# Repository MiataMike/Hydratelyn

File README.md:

# Hydratelyn
This project is a soil moisture sensor that can be interfaced to a MyDAQ, or just about any DAQ with a voltage input

## Probe selection
Most soil probes are made from PCB material, with ENIG plating (at best), which corrodes over time due to electrolysis
Hydratelyn uses 2mm pencil leads as the probes, which won't rust. The resistance of the probes was measured around 15 Ohms
from end to end, which is insignificant relative to the resistance of the soil

## Soil resistance
To figure out what resistance range we're trying to measure, I placed 2 leads in my plants' soil while it was dry and checked with a multimeter. It read 30M, which is very high. After watering it dropped to 7k.

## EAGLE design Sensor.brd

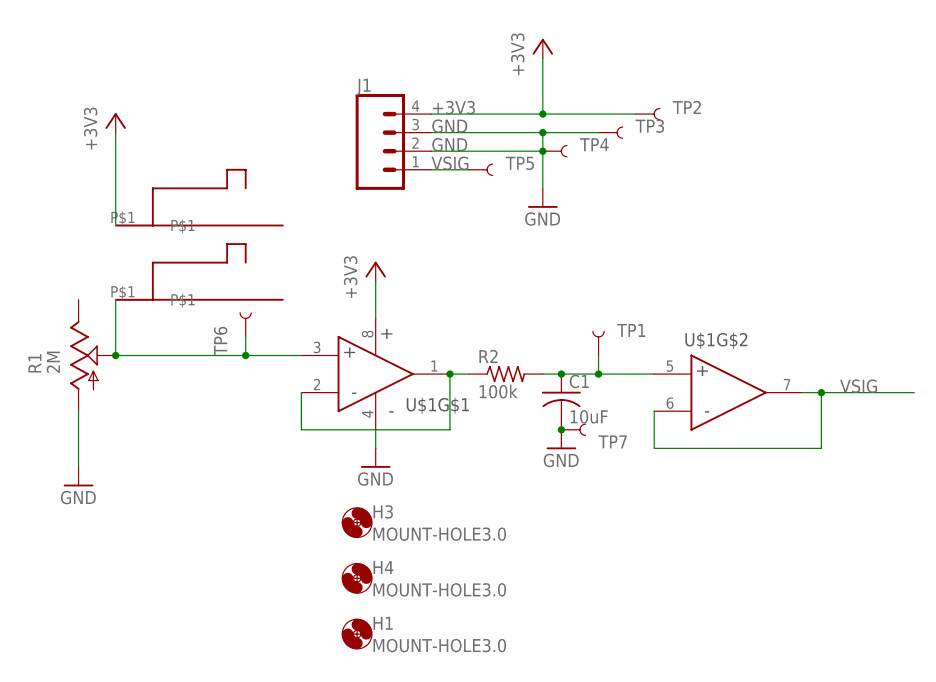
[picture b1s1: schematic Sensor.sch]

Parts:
C1: 10uF; C1206
H1, H3, H4: MOUNT-HOLE3.0; 3,0
J1: CONN_04SCREW; SCREWTERMINAL-3.5MM-4
R1: 2M; CT6
R2: 100k; R1206
TP1, TP2, TP3, TP4, TP5, TP6, TP7: TEST-POINT3X5; PAD.03X.05
U$1: TLV9102; SOIC-8
U$2, U$3: 709155001610004

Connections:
+3V3: J1.4, TP2.P$1, U$1.8 (V+), U$2.P$1
GND: C1.2, J1.2, J1.3, R1.A, TP3.P$1, TP4.P$1, TP7.P$1, U$1.4 (V-)
unnamed: C1.1, R2.2, TP1.P$1, U$1.5 (+)
unnamed: R1.S, TP6.P$1, U$1.3 (NONINVERTING), U$3.P$1
unnamed: R2.1, U$1.1 (OUT), U$1.2 (INVERTING)
VSIG: J1.1, TP5.P$1, U$1.6 (-), U$1.7 (OUT)

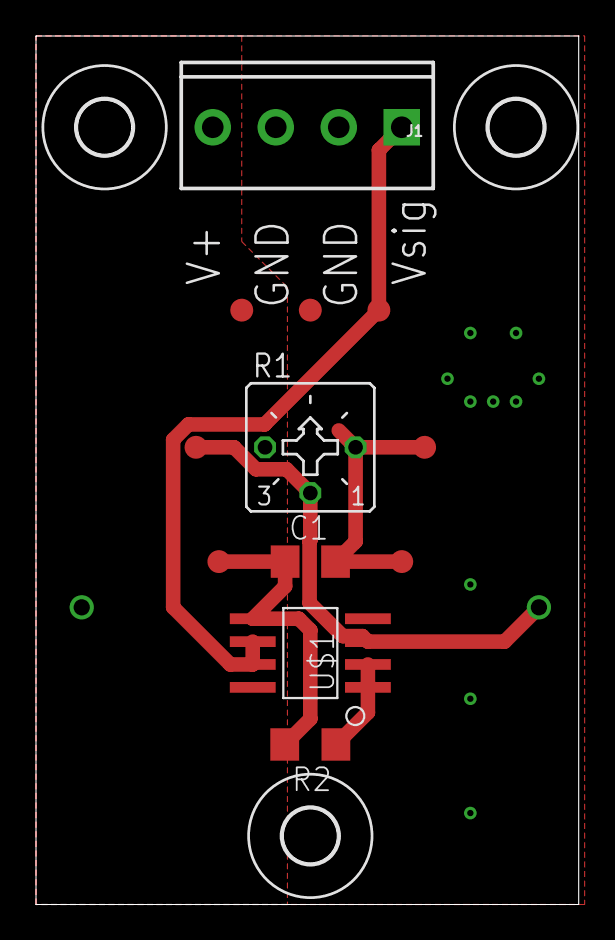
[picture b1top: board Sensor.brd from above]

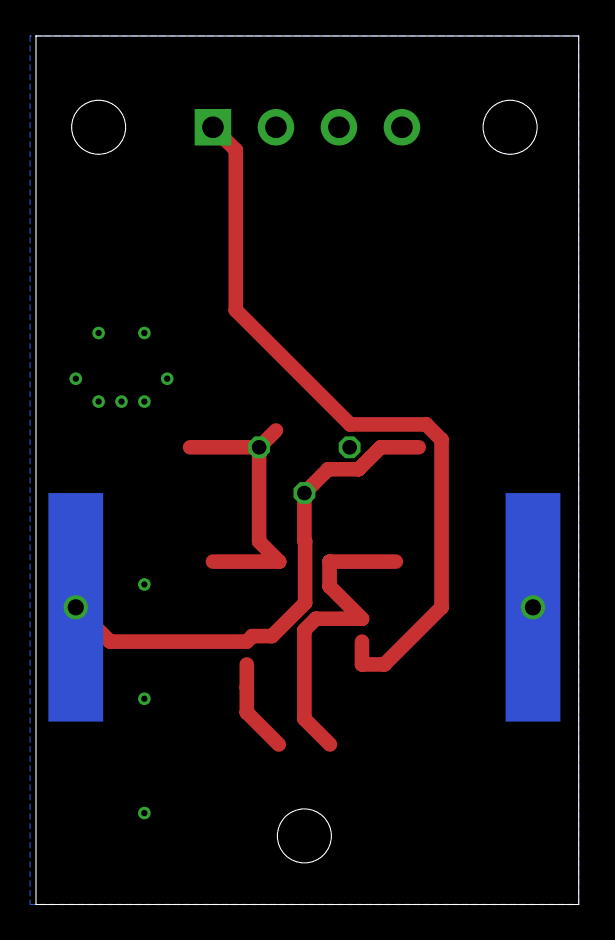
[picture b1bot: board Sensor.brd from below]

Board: 2 copper layers, 30.1 x 48.2 mm, 17 parts (2 on the bottom side), 6 nets.

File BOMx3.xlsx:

Index | Quantity | Part Number | Manufacturer Part Number | Description | Customer Reference | Available | Backorder | Unit Price | Extended Price USD
1 | 3 | CT6EP205-ND | CT6EP205 | TRIMMER 2M OHM 0.5W PC PIN TOP |  | 3 | 0 | 0.78000 | 2.34
2 | 10 | 36-9900-ND | 9900 | MACHINE SCREW PAN PHILLIPS 4-40 |  | 10 | 0 | 0.10000 | 1.00
3 | 10 | 36-4694-ND | 4694 | HEX NUT 3/16" STEEL 4-40 |  | 10 | 0 | 0.10000 | 1.00
4 | 3 | 296-TLV9102IDRCT-ND | TLV9102IDR | IC OPAMP POWER 2 CIRCUIT 8SOIC |  | 3 | 0 | 1.00000 | 3.00
5 | 6 | 478-8741-1-ND | 709155001610004 | CONN SPRING BATTERY 1POS SMD |  | 6 | 0 | 0.26000 | 1.56
6 | 3 | 277-1860-ND | 1984633 | TERM BLK 4POS SIDE ENT 3.5MM PCB |  | 3 | 0 | 0.95000 | 2.85
7 | 5 | 1276-1075-1-ND | CL31A106KAHNNNE | CAP CER 10UF 25V X5R 1206 |  | 5 | 0 | 0.20000 | 1.00
8 | 10 | RMCF1206FT100KCT-ND | RMCF1206FT100K | RES 100K OHM 1% 1/4W 1206 |  | 10 | 0 | 0.03100 | 0.31

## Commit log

2020-12-05 Made board, passes DRC, gerbers generated
2020-12-06 Changed board dimensions
2020-12-06 Added simulation files
2020-12-06 Added cart from digikey, updated schematic with values
2020-12-15 added files for board holder, renamed zip

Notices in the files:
parts and their libraries:
SparkFun-Connectors: Licensing: Creative Commons ShareAlike 4.0 International - https://creativecommons.org/licenses/by-sa/4.0
